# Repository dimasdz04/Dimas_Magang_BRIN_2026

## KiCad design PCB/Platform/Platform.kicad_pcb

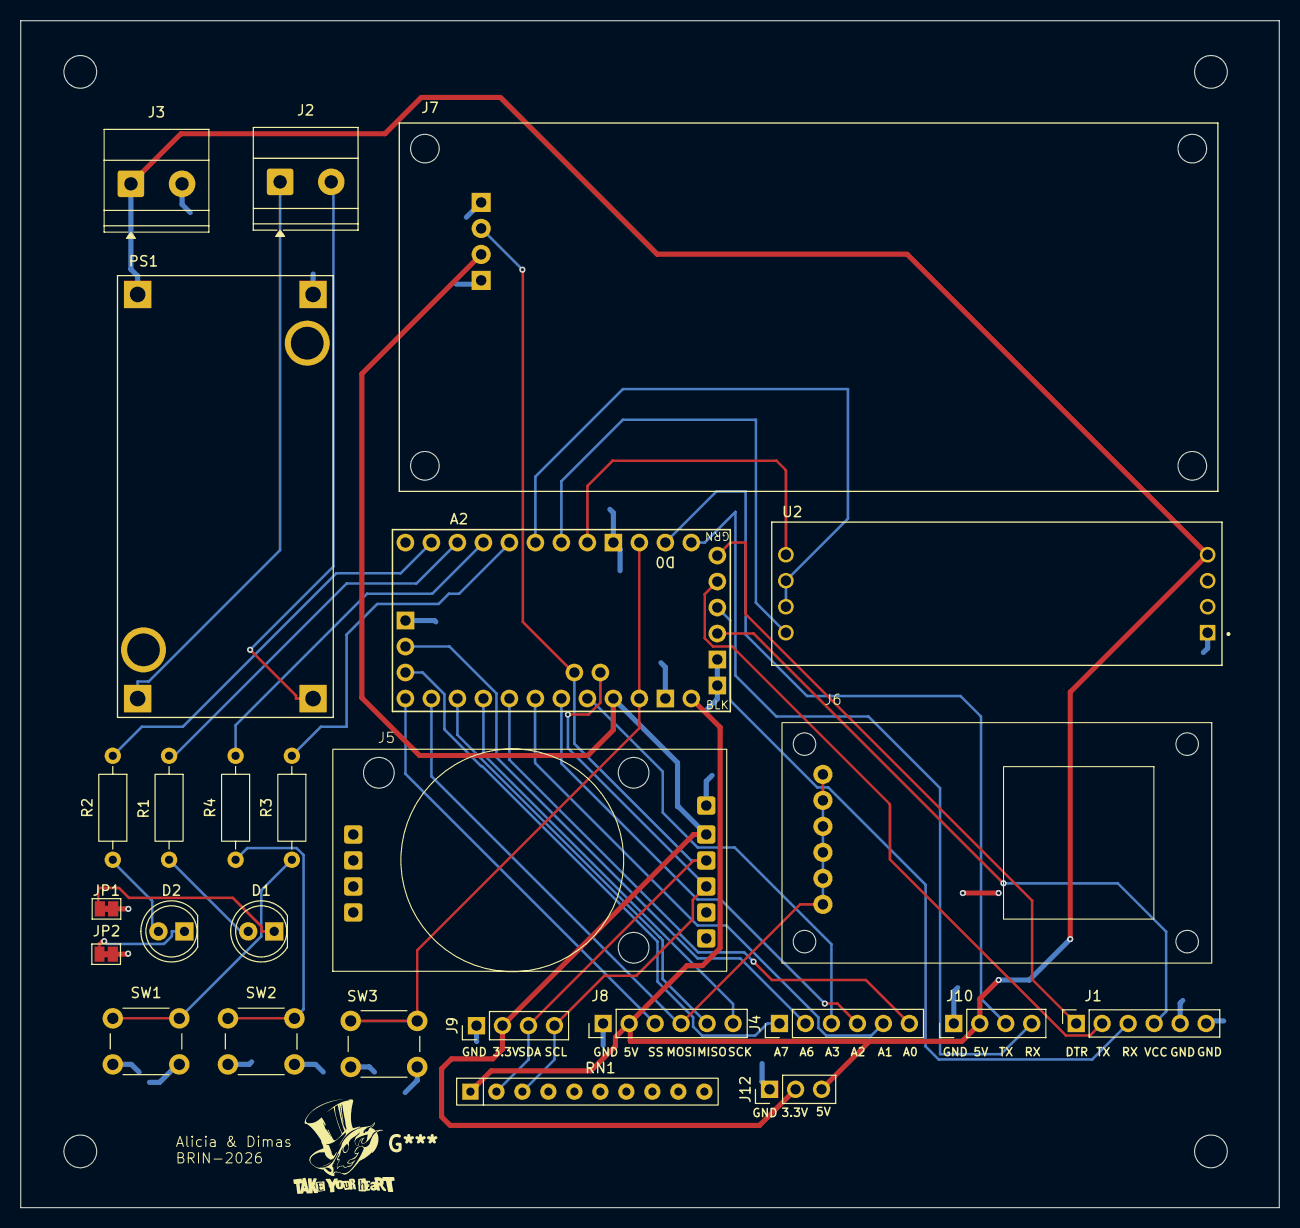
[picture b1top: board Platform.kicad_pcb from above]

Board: 2 copper layers, 123.0 x 116.0 mm, 26 parts (0 on the bottom side), 37 nets.

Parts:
A2: Clone_Pro_Mini_Socket
D1, D2: LED; LED_D5.0mm
J1: Program; PinSocket_1x06_P2.54mm_Vertical
J2, J3: Conn_01x02_Pin; TerminalBlock_Phoenix_MKDS-1,5-2_1x02_P5.00mm_Horizontal
J4: Pin_Analog; PinHeader_1x06_P2.54mm_Vertical
J5: Pin_RTC; DS3231
J6: Micro_SD_Card; modul sdcard
J7: Pin_LCD; MODULE_LCD-16X2
J8: Pin_SPI_1; PinHeader_1x06_P2.54mm_Vertical
J9: Pin_I2C_eksternal; PinHeader_1x04_P2.54mm_Vertical
J10: Pin_SERIAL; PinHeader_1x04_P2.54mm_Vertical
J12: PWR External; PinHeader_1x03_P2.54mm_Vertical
JP1, JP2: SolderJumper_2_Bridged; SolderJumper-2_P1.3mm_Bridged_Pad1.0x1.5mm
PS1: LM2596; CONV_MC00100
R1, R2: 220Ω; R_Axial_DIN0207_L6.3mm_D2.5mm_P10.16mm_Horizontal
R3, R4: 1kΩ; R_Axial_DIN0207_L6.3mm_D2.5mm_P10.16mm_Horizontal
RN1: R_Network09_US; R_Array_SIP10
SW1, SW2: SW_Push; SW_PUSH_6mm
SW3: RST; SW_PUSH_6mm
U2: MAX485_MODULE_5V_LOGIC_TLL_TO_RS-485_CONVERTER; MODULE_MAX485_MODULE_5V_LOGIC_TLL_TO_RS-485_CONVERTER

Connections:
+3.3V: A2.Vcc1 (Vcc), J5.2, J7.2, J9.2, J12.2
+5V: A2.RAW, J3.1, J8.2, J10.2, J12.3, PS1.OUT+, RN1.1 (common), U2.4 (VCC)
/A0: A2.A0, J4.6
/A1: A2.A1, J4.5
/A2: A2.A2, J4.4
/A3: A2.A3, J4.3
/A6: A2.A6, J4.2
/A7: A2.A7, J4.1
/I2C_UART_BUS.RX: A2.D1 (D1/TX), J10.4
/I2C_UART_BUS.SCL: A2.A5 (A5/SCL), J5.4, J9.4, RN1.3 (R2)
/I2C_UART_BUS.SDA: A2.A4 (A4/SDA), J5.3, J7.3, J9.3, RN1.2 (R1)
/I2C_UART_BUS.TX: A2.D0 (D0/RX), J10.3
/IO_BUS.BTN1: A2.D5, R3.1
/IO_BUS.BTN2: A2.D6, R4.1
/IO_BUS.LED1: A2.D7, R1.1
/IO_BUS.LED2: A2.D8, R2.1
/RS485_CTRL: A2.D4, U2.6 (RE), U2.7 (DE)
/RS485_RX: A2.D2 (D2_INT0), U2.5 (RO)
/RS485_TX: A2.D3 (D3_INT1), U2.8 (DI)
/RST: A2.RST1 (RESET), A2.RST2 (RESET), SW3.1
/SPI_BUS.MISO: A2.D12 (D12_MISO), J8.5
/SPI_BUS.MOSI: A2.D11 (D11_MOSI), J6.3 (CMD_3), J8.4
/SPI_BUS.SCK: A2.D13 (D13_SCK), J8.6
/SPI_BUS.SS: A2.D10 (D10_CS), J8.3
/V_RAW: J2.1, PS1.IN+
GND: A2.GND1 (GND), A2.GND2 (GND), A2.GND3 (GND), A2.GND4 (GND), A2.GND5 (GND), J1.5, J1.6, J3.2, J5.1, J7.1, J8.1, J9.1, J10.1, J12.1, JP1.2 (B), JP2.2 (B), PS1.OUT-, SW1.2, SW2.2, SW3.2, U2.1 (GND)
unnamed: A2.DTR (~DTR), J1.1
unnamed: D1.2 (A), R1.2
unnamed: D1.1 (K), JP1.1 (A)
unnamed: D2.2 (A), R2.2
unnamed: D2.1 (K), JP2.1 (A)
unnamed: A2.TXO, J1.2
unnamed: A2.RXI, J1.3
unnamed: A2.Vcc2 (Vcc), J1.4
unnamed: J2.2, PS1.IN-
unnamed: R3.2, SW1.1
unnamed: R4.2, SW2.1

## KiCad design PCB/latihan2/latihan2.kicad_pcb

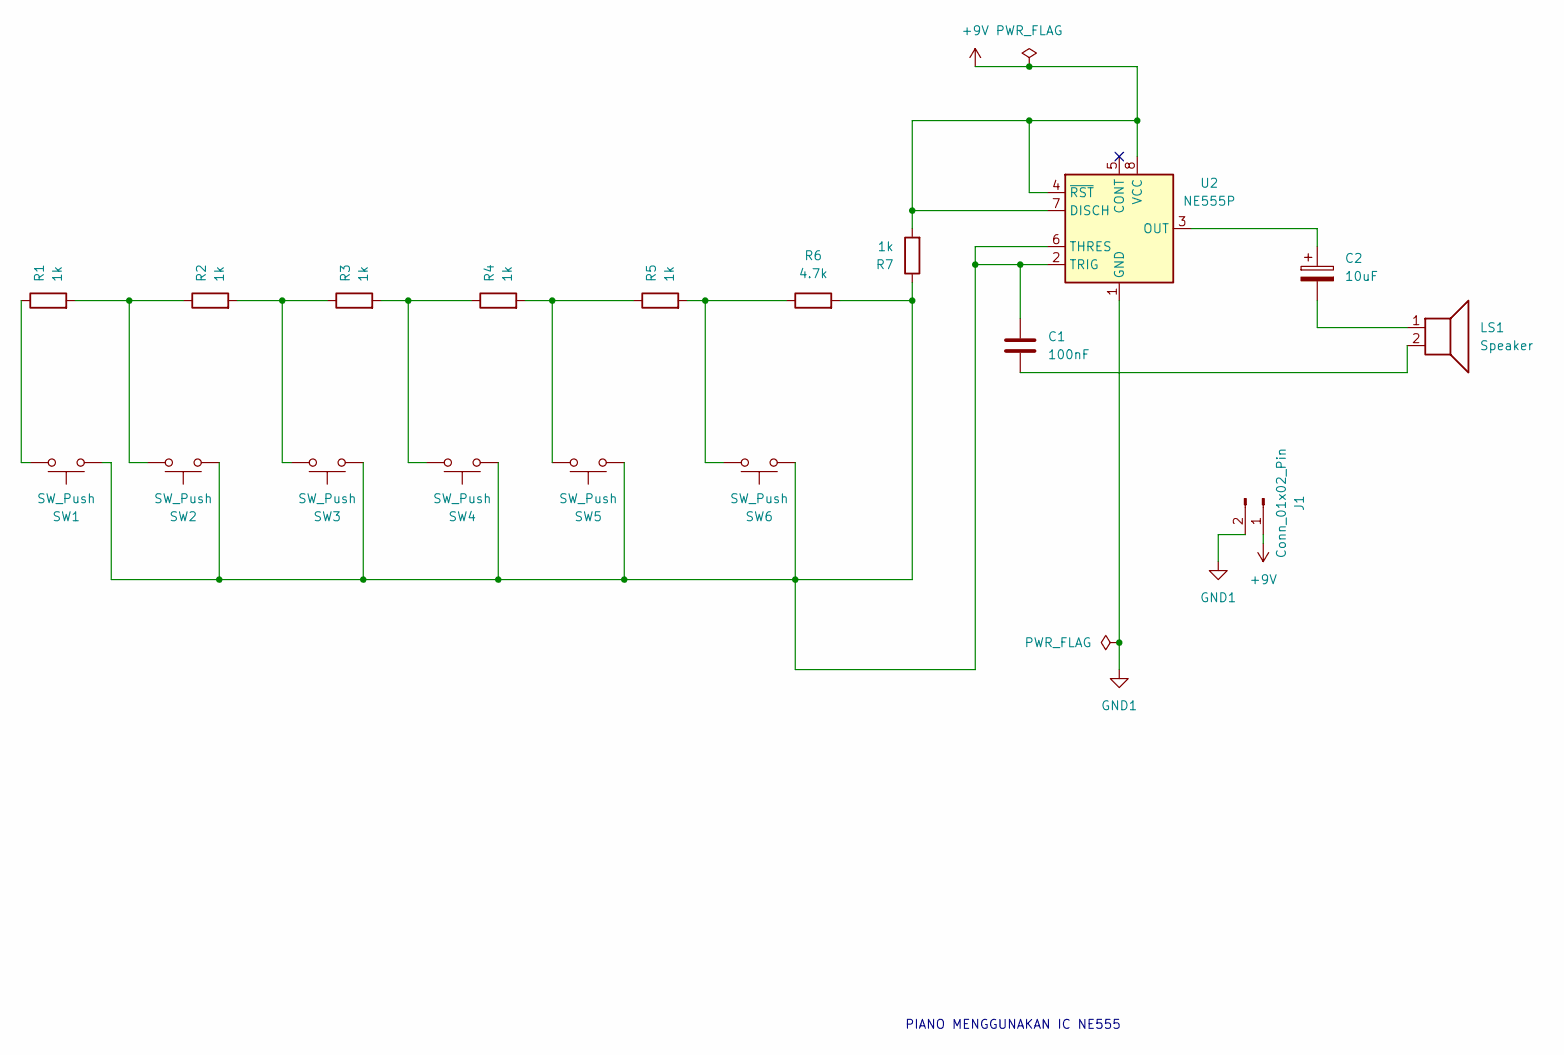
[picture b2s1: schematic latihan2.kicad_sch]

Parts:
C1: 100nF; C_Disc_D5.0mm_W2.5mm_P5.00mm
C2: 10uF; CP_Radial_D5.0mm_P2.50mm
J1: Conn_01x02_Pin; PinHeader_1x02_P2.54mm_Vertical
LS1: Speaker; PinHeader_1x02_P2.54mm_Vertical
R1, R2, R3, R4, R5, R7: 1k; R_Axial_DIN0207_L6.3mm_D2.5mm_P10.16mm_Horizontal
R6: 4.7k; R_Axial_DIN0207_L6.3mm_D2.5mm_P10.16mm_Horizontal
SW1, SW2, SW3, SW4, SW5, SW6: SW_Push; SW_PUSH_6mm_H5mm
U2: NE555P; DIP-8_W7.62mm

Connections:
+9V: J1.1, R7.2, U2.4 (~RST), U2.7 (DISCH), U2.8 (VCC)
GND1: J1.2, U2.1 (GND)
unnamed: C1.2, LS1.2
unnamed: C2.2, LS1.1
unnamed: R1.1, SW1.1
unnamed: R1.2, R2.1, SW2.1
unnamed: R2.2, R3.1, SW3.1
unnamed: R3.2, R4.1, SW4.1
unnamed: R4.2, R5.1, SW5.1
unnamed: R5.2, R6.1, SW6.1
unnamed: C2.1, U2.3 (OUT)
unnamed: C1.1, R6.2, R7.1, SW1.2, SW2.2, SW3.2, SW4.2, SW5.2, SW6.2, U2.2 (TRIG), U2.6 (THRES)

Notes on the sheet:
PIANO MENGGUNAKAN IC NE555

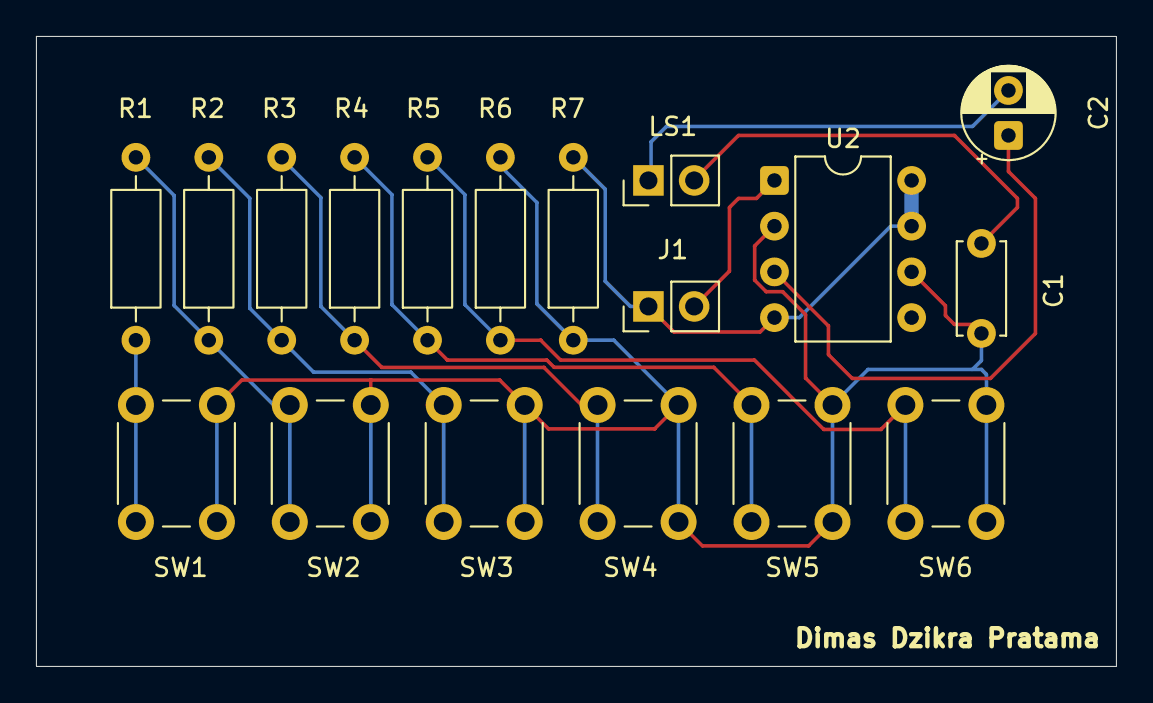
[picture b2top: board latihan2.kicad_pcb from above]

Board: 2 copper layers, 60.0 x 35.0 mm, 18 parts (0 on the bottom side), 12 nets.
